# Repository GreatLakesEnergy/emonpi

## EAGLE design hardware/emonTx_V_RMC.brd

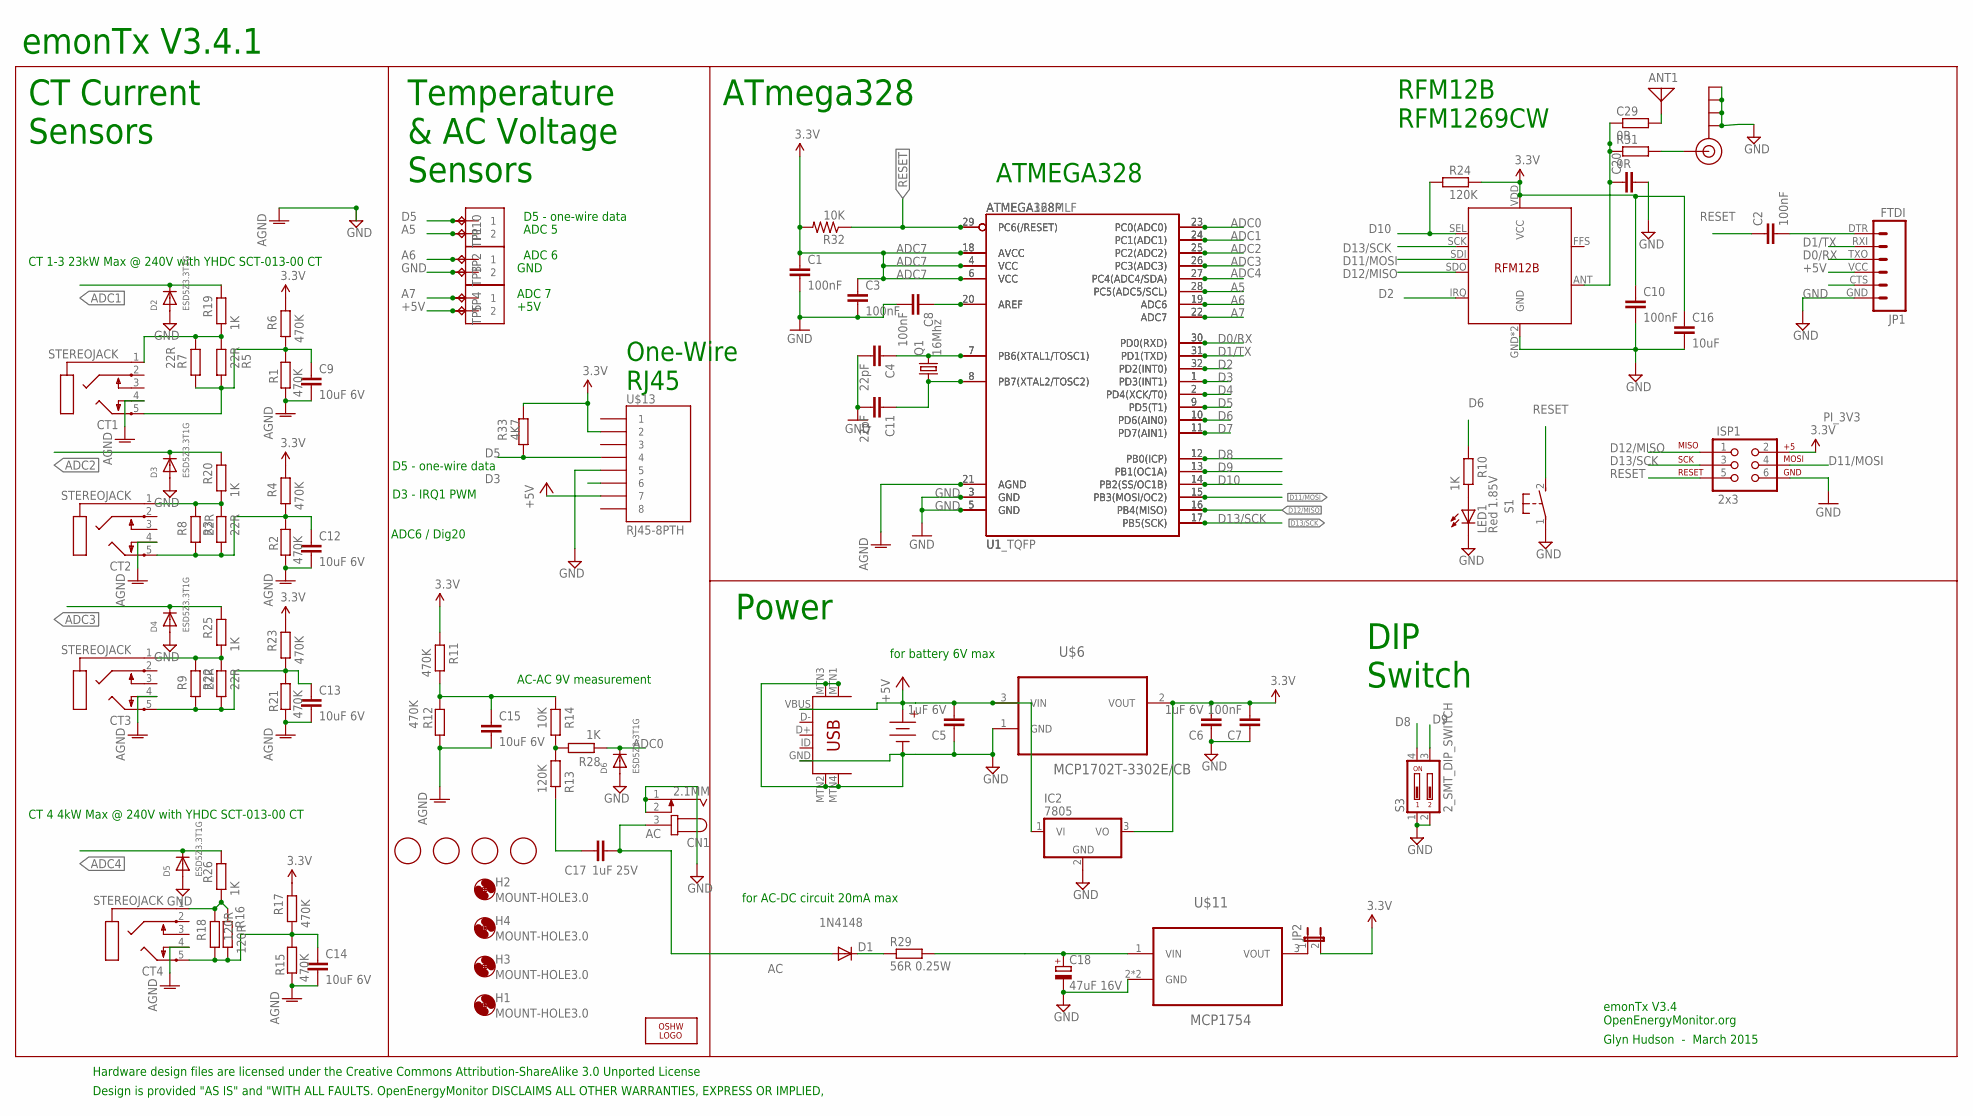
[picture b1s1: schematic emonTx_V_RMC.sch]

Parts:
ANT1: ANTENNA; PAD-01
C1, C2, C3, C7, C8, C10: 100nF; C0603
C4, C11: 22pF; C0603
C5, C6: 1uF 6V; C0603
C9, C12, C13, C14, C15: 10uF 6V; C0603
C16: 10uF; C0603
C17: 1uF 25V; C0603
C18: 47uF 16V; PANASONIC_D
C20: ant tune?; C0603
C29: 0R; R0603
CN1: 2.1MM; SPC4077
CT1, CT2, CT3, CT4: STEREOJACK; STX3100
D1: 1N4148; SOD-323
D2, D3, D4, D5, D6: ESD5Z3.3T1G; SOD-523
H1, H2, H3, H4: MOUNT-HOLE3.0; 3,0
IC2: 7805; TO220V
ISP1: 2x3; 2X3
J3, J5, J6: 1X2-3.5MM
J$1: SMA_EDGE; SMA-EDGE
JP1: FTDI; FTDI_BASIC
JP2: JUMPER-2PTH_LOCK; 1X02_LOCK
LED1: Red 1.85V; CHIP-LED0805
LOGO1: OSHW_LOGO_6MILX0200-NT; OSHW_6X200_NOTEXT
Q1: 16Mhz; HC49UP
R1, R2, R4, R6, R11, R12, R15, R17, R21, R23: 470K; R0603
R3, R5, R22: 22R; 0204/7
R7, R8, R9: 22R; R1206
R10, R19, R20, R25, R26, R28: 1K; R0603
R13, R24: 120K; R0603
R14, R32: 10K; R0603
R16: 120R; 0204/7
R18: 120R; R1206
R29: 56R 0.25W; R1206
R31: 0R; R0603
R33: 4K7; R0603
S1: 31-XX; B3F-31XX
S3: 2_SMT_DIP_SWITCH; DIP_SWITCH_SMT
TP1, TP2, TP3, TP4, TP5, TP10: TPPAD1-13; P1-13
U1: ATMEGA168MLF; MLF32
U1_TQFP: ATMEGA328P; TQFP32-08
U$1, U$4, U$5, U$7: FIDUCIAL; FIDUCIAL_1MM
U$3: 4.5V; AAA_PCB_HOLDER
U$6: MCP1702T-3302E/CB; SOT95P237X112-3N
U$10: USB-MINIB-5PIN; USB-MINIB-CISECO
U$11: MCP1754; SOT89
U$13: RJ45-8PTH; RJ45-8
U$14: RFM12B

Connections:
+5V: C5.2, IC2.1 (VI), J6.2, JP1.VCC (4), TP5.TP, U$3.+, U$6.3 (VIN), U$10.VBUS, U$13.7
A5: J3.2, TP1.TP, U1.28 (PC5(ADC5/SCL)), U1_TQFP.28 (PC5(ADC5/SCL))
A6: J5.1, TP2.TP, U1.19 (ADC6), U1_TQFP.19 (ADC6)
A7: J6.1, TP4.TP, U1.22 (ADC7), U1_TQFP.22 (ADC7)
AC: C17.2, CN1.3, D1.2 (A)
ADC0: D6.K (C), R28.1, U1.23 (PC0(ADC0)), U1_TQFP.23 (PC0(ADC0))
ADC1: D2.K (C), R19.2, U1.24 (PC1(ADC1)), U1_TQFP.24 (PC1(ADC1))
ADC2: D3.K (C), R20.2, U1.25 (PC2(ADC2)), U1_TQFP.25 (PC2(ADC2))
ADC3: D4.K (C), R25.2, U1.26 (PC3(ADC3)), U1_TQFP.26 (PC3(ADC3))
ADC4: D5.K (C), R26.2, U1.27 (PC4(ADC4/SDA)), U1_TQFP.27 (PC4(ADC4/SDA))
ADC7: C1.1, C3.1, C6.2, C7.2, C10.1, C16.1, IC2.3 (VO), ISP1.2, JP2.2, R4.2, R6.2, R11.2, R17.2, R23.2, R24.2, R32.2, R33.1, U1.4 (VCC), U1.6 (VCC), U1.18 (AVCC), U1_TQFP.4 (VCC), U1_TQFP.6 (VCC), U1_TQFP.18 (AVCC), U$6.2 (VOUT), U$13.2, U$14.VDD (VCC)
AGND: C9.2, C12.2, C13.2, C14.2, C15.2, CT1.4, CT2.4, CT3.4, CT4.4, R1.2, R2.2, R12.1, R15.2, R21.2, U1.21 (AGND), U1_TQFP.21 (AGND)
D0/RX: JP1.TXO (3), U1.30 (PD0(RXD)), U1_TQFP.30 (PD0(RXD))
D1/TX: JP1.RXI (2), U1.31 (PD1(TXD)), U1_TQFP.31 (PD1(TXD))
D2: U1.32 (PD2(INT0)), U1_TQFP.32 (PD2(INT0)), U$14.IRQ
D3: U1.1 (PD3(INT1)), U1_TQFP.1 (PD3(INT1)), U$13.6
D4: U1.2 (PD4(XCK/T0)), U1_TQFP.2 (PD4(XCK/T0))
D5: J3.1, R33.2, TP10.TP, U1.9 (PD5(T1)), U1_TQFP.9 (PD5(T1)), U$13.4
D6: R10.2, U1.10 (PD6(AIN0)), U1_TQFP.10 (PD6(AIN0))
D7: U1.11 (PD7(AIN1)), U1_TQFP.11 (PD7(AIN1))
D8: S3.4, U1.12 (PB0(ICP)), U1_TQFP.12 (PB0(ICP))
D9: S3.3, U1.13 (PB1(OC1A)), U1_TQFP.13 (PB1(OC1A))
D10: R24.1, U1.14 (PB2(SS/OC1B)), U1_TQFP.14 (PB2(SS/OC1B)), U$14.SEL
D11/MOSI: ISP1.4, U1.15 (PB3(MOSI/OC2)), U1_TQFP.15 (PB3(MOSI/OC2)), U$14.SDI
D12/MISO: ISP1.1, U1.16 (PB4(MISO)), U1_TQFP.16 (PB4(MISO)), U$14.SDO
D13/SCK: ISP1.3, U1.17 (PB5(SCK)), U1_TQFP.17 (PB5(SCK)), U$14.SCK
DIG1: C20.1, C29.1, R31.1, U$14.ANT
GND: C1.2, C3.2, C4.2, C5.1, C6.1, C7.1, C8.2, C10.2, C11.2, C16.2, C18.-, C20.2, CN1.1, CN1.2, D2.A, D3.A, D4.A, D5.A, D6.A, IC2.2 (GND), ISP1.6, J5.2, J$1.GND@0 (GND), J$1.GND@1 (GND), J$1.GND@2 (GND), J$1.GND@3 (GND), JP1.GND (6), LED1.C, S1.1, S3.1, S3.2, TP3.TP, U1.3 (GND), U1.5 (GND), U1_TQFP.3 (GND), U1_TQFP.5 (GND), U$3.-, U$6.1 (GND), U$10.GND, U$10.MTN1 (MTN2), U$10.MTN2 (MTN3), U$10.MTN3 (MTN1), U$10.MTN4, U$11.2 (GND), U$11.2.1 (GND), U$13.5, U$14.GND, U$14.P$12 (GND)
unnamed: C4.1, Q1.2, U1.7 (PB6(XTAL1/TOSC1)), U1_TQFP.7 (PB6(XTAL1/TOSC1))
unnamed: CT1.1, R5.2, R7.2, R19.1
unnamed: C13.1, CT3.5, R9.1, R21.1, R22.1, R23.1
unnamed: R13.2, R14.1, R28.2
unnamed: JP2.1, U$11.3 (VOUT)
unnamed: C18.+, R29.2, U$11.1 (VIN)
unnamed: C17.1, R13.1
unnamed: CT4.1, R16.2, R18.2, R26.1
unnamed: C11.1, Q1.1, U1.8 (PB7(XTAL2/TOSC2)), U1_TQFP.8 (PB7(XTAL2/TOSC2))
unnamed: CT2.1, R3.2, R8.2, R20.1
unnamed: ANT1.1, C29.2
unnamed: D1.1 (C), R29.1
unnamed: CT3.1, R9.2, R22.2, R25.1
unnamed: C8.1, U1.20 (AREF), U1_TQFP.20 (AREF)
unnamed: C2.2, JP1.DTR (1)
unnamed: J$1.SIG (SIGNAL), R31.2
unnamed: C12.1, CT2.5, R2.1, R3.1, R4.1, R8.1
unnamed: C15.1, R11.1, R12.2, R14.2
unnamed: C14.1, CT4.5, R15.1, R16.1, R17.1, R18.1
unnamed: C9.1, CT1.5, R1.1, R5.1, R6.1, R7.1
unnamed: LED1.A, R10.1
RESET: C2.1, ISP1.5, R32.1, S1.2 (S), U1.29 (PC6(/RESET)), U1_TQFP.29 (PC6(/RESET))

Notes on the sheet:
AC-AC 9V measurement
emonTx V3.4 OpenEnergyMonitor.org
Glyn Hudson - March 2015
CT 4 4kW Max @ 240V with YHDC SCT-013-00 CT
CT 1-3 23kW Max @ 240V with YHDC SCT-013-00 CT
for battery 6V max
for AC-DC circuit 20mA max
Power
ATmega328
CT Current Sensors
Temperature & AC Voltage Sensors
Design is provided "AS IS" and "WITH ALL FAULTS. OpenEnergyMonitor DISCLAIMS ALL OTHER WARRANTIES, EXPRESS OR IMPLIED,
Hardware design files are licensed under the Creative Commons Attribution-ShareAlike 3.0 Unported License
emonTx V3.4.1
ADC 5
D5 - one-wire data
ADC 6
ATMEGA328
RFM12B RFM1269CW
One-Wire RJ45
D3 - IRQ1 PWM
ADC6 / Dig20
DIP Switch
ADC 7
GND
+5V

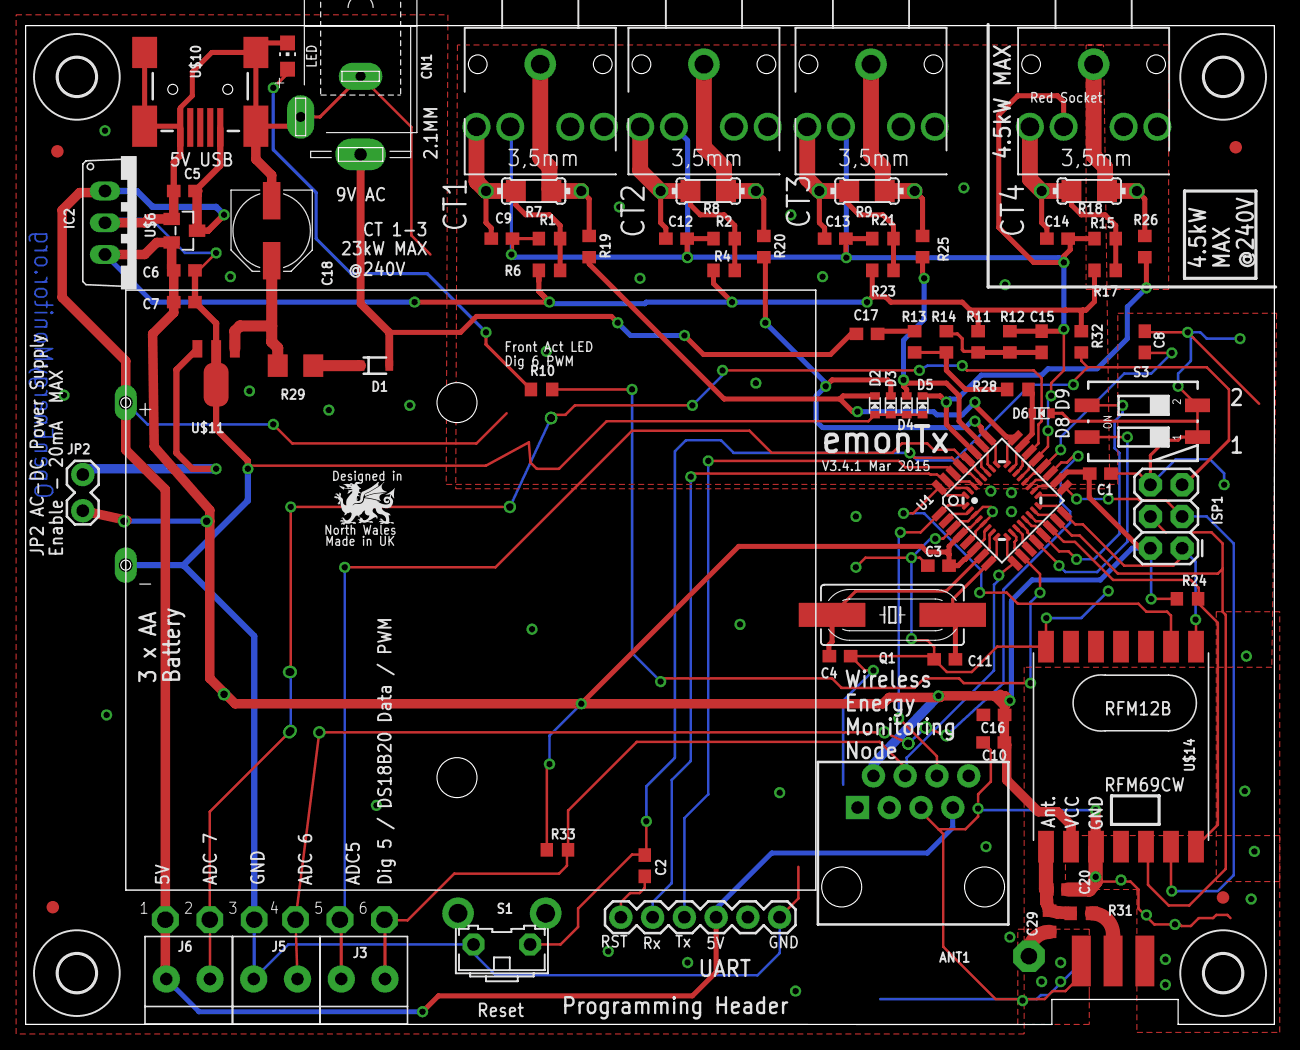
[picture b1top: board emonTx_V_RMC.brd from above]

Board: 2 copper layers, 99.9 x 79.9 mm, 98 parts (1 on the bottom side), 50 nets.

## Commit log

2015-03-01 Initializing default redis values to fix bug
2015-12-22 Updated LCD file to communicate with bbb using i2c 2
2015-12-22 Updadeted LCD files to work with bbb
2016-07-05 Update install_wifi_autorest.sh
    reboot cancel install process.
2016-07-07 Cleaning repo and fixing bugs in wifi autoreset
2016-07-07 removing typing error
2016-07-11 changes to emonpi lcd emonPiLCD.py to take arguments from config file, that path of which is given as terminal line argument in emonpilcd- service
2016-07-13 few fixes to the new .conf version. Fixed node ID, RMC running again
2016-07-13 fixed missing msg to log output
2016-07-18 adding reset bash script for monit
2016-07-19 adding ui status
2016-07-21 mod gitignore
2016-07-22 updating repo everyday
2016-07-22 Updating emonhub
2016-07-22 disabling unnecessary services, fixing some bugs
2016-07-23 Add ConfigDownloader to download emonpo config file from the server
    The config will be generated on the server and can be downloaded from
    the client if not available (for example during the first run).
    We need to make sure that the config is downloaded through a secure
    connection.
2016-07-24 Add download exception handling
    download() now returns true/false
    download exception is availbale through the error attribute.
2016-07-24 Add exception handling for file write operation
    save() now returns True/False. A possible exception is availbe through the error
    attribute.
    This also adds unicode support
2016-07-25 adding HallSensor .h file and class .cpp file. and changes to main arduino file to read dc current and send via serial according to .conf protocol
2016-07-25 new version of arduino compiled hex which is uploaded to emonTx by the upload thing.
2016-07-25 Always install release version
2016-07-26 commenting out lcd config path as this should be an env variable
2016-07-26 Verified this running version including precise measurement of 3.3V ADC reference
2016-07-26 install emonhub v0.5.1 and checking update in RELEASE Version
2016-07-26 Tidied up the code, optimised out a few longs and floats, skipped some unnecessary conditional
2016-07-26 install emonhub RELEASE Version
2016-07-26 converting to integer to fix bug
2016-07-27 up to date version of board schematic
2016-07-27 Fixing some bugs
2016-07-28 reboot GPRS modem if monit fail to bring connection back
2016-07-29 adding more defaults
2016-07-29 fixing gprs signal initialziatoin in redis causing freezing
2016-08-02 changes to emonPi_Atmel code and hex file to add DC power to package.
2016-08-03 adding version file for update tracking
2016-08-04 LCD names and units from emonhub
2016-08-04 LCD display names and units from emonhub
2016-08-04 updating lcd script to the latest
2016-08-04 a few changes to emonTx i made during calibration. current version seems to be not working so re-uploading working version
2016-08-10 changes to newest version. few more screw turns
2016-08-22 initial working version of with auto-downloading
2016-08-22 Setting up emonhub config from ansible
2016-08-25 updating emonhub.conf url and adding downloading status on lcd
2016-08-26 Updating tags during updates
2016-09-08 checking updates before updating RMC
2016-09-08 fixing md5sum syntax
2016-10-09 Adding 3g modem status on LCD and auto connect
2016-10-09 Adding 3g modem reset file
2016-10-09 Adding 3G modem on our RMC
    This is tested on HUAWEI E303; i will test it with another modem if i get one.

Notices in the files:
parts and their libraries:
SparkFun-DigitalIC: Licensing: CC v3.0 Share-Alike You are welcome to use this library for commercial purposes.
microbuilder: This work is placed in the public domain, and may be freely used for commercial and non-commercial work with the following conditions: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
